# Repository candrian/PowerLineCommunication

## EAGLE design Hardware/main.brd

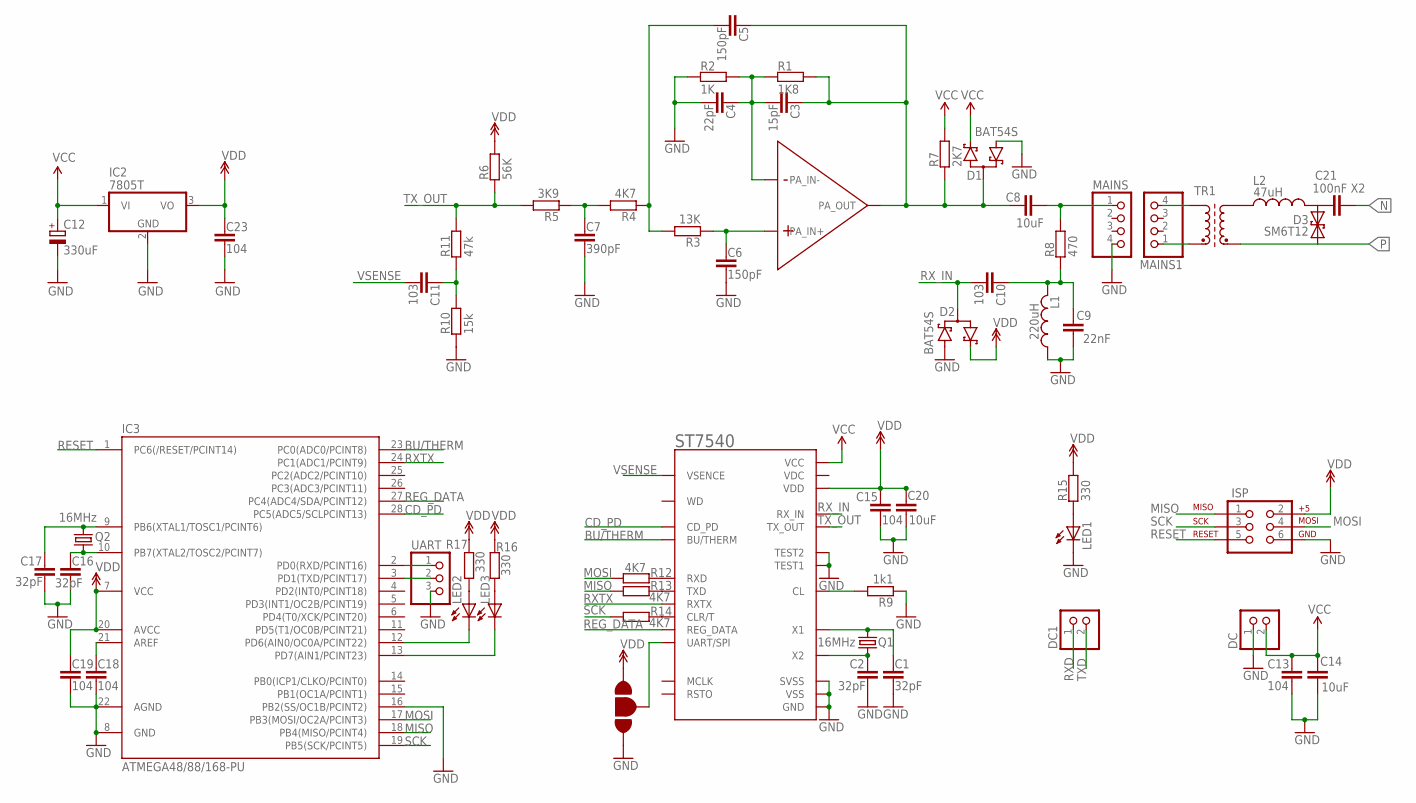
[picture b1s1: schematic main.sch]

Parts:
C1, C2, C16, C17: 32pF; C-22X55(FAKI)
C3: 15pF; C-22X55(FAKI)
C4: 22pF; C-22X55(FAKI)
C5: 150pF; C-22X55(FAKI)
C6: 150pF; C-25X8(FAKI)
C7: 390pF; C-25X8(FAKI)
C8: 10uF; C-25X8(FAKI)
C9: 22nF; C-22X6(FAKI)
C10, C11: 103; C-25X8(FAKI)
C12: 330uF; TT2D6
C13, C15, C18, C19: 104; C-22X6(FAKI)
C14, C20: 10uF; C-22X55(FAKI)
C21: 100nF X2; C-22X6(FAKI)
C23: 104; C-22X55(FAKI)
D1, D2: BAT54S; SOT23
D3: SM6T12; F126Z12
DC, DC1: PINHD-1X2; 1X02
IC1: ST7540BREAKOUT; ST7540-BREAKOUT
IC2: 7805T; TO220H
IC3: ATMEGA48/88/168-PU; DIL28-3
ISP: AVR-ISP-6
JP2: PCB-JUMPER-3
L1: 220uH; L-2.2MH-DIP
L2: 47uH; L-2.2MH-DIP
LED1, LED2, LED3: LED3MM
MAINS, MAINS1: PINHD-1X4; 1X04
Q1, Q2: 16MHz; HC49US
R1: 1K8; R0207/12
R2: 1K; R0207/12
R3: 13K; R0207/12
R4: 4K7; R0207/12
R5: 3K9; R0207/12
R6: 56K; R0207/12
R7: 2K7; R0207/12
R8: 470; R0207/12
R9: 1k1; R0207/12
R10: 15k; R0207/12
R11: 47k; R0207/12
R12, R13, R14: 4K7; R0270/10
R15, R16, R17: 330; R0270/10
TR1: SM-T4
UART: PINHD-1X3; 1X03

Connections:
12V: C15.1, C19.1, C20.1, C23.1, D2.2 (C2), IC1.VDD, IC2.3 (VO), IC3.7 (VCC), IC3.20 (AVCC), ISP.2, JP2.P$1 (1), R6.2, R15.2, R16.2, R17.2
BU/THERM: IC1.BU/THERM, IC3.23 (PC0(ADC0/PCINT8))
CD_PD: IC1.CD_PD, IC3.28 (PC5(ADC5/SCLPCINT13))
GND: C1.2, C2.2, C4.2, C6.2, C7.2, C9.1, C12.-, C13.2, C14.2, C15.2, C16.2, C17.2, C18.2, C19.2, C20.2, C23.2, D1.1 (A1), D2.1 (A1), DC.1, IC1.GND, IC1.SVSS, IC1.TEST1, IC1.TEST2, IC1.VSS, IC2.2 (GND), IC3.8 (GND), IC3.16 (PB2(SS/OC1B/PCINT2)), IC3.22 (AGND), ISP.6, JP2.P$3 (3), L1.P$1 (1), LED1.K (C), MAINS.4, R2.1, R9.1, R10.1, UART.3
MISO: IC3.18 (PB4(MISO/PCINT4)), ISP.1, R13.1
MOSI: IC3.17 (PB3(MOSI/OC2A/PCINT3)), ISP.4, R12.1
N: C21.1
unnamed: C1.1, IC1.X1, Q1.1
unnamed: C2.1, IC1.X2, Q1.2
unnamed: C3.1, C5.1, C8.1, D1.3 (C1A2), IC1.PA_OUT, R1.2, R7.1
unnamed: C3.2, C4.1, IC1.PA_IN-, R1.1, R2.2
unnamed: C5.2, R3.2, R4.1
unnamed: C6.1, IC1.PA_IN+, R3.1
unnamed: C8.2, MAINS.1, R8.2
unnamed: C7.1, R4.2, R5.1
unnamed: C9.2, C10.1, L1.P$2 (2), R8.1
unnamed: C11.1, R10.2, R11.1
unnamed: IC1.CL, R9.2
unnamed: IC1.UART/SPI, JP2.P$2 (2)
unnamed: C16.1, IC3.10 (PB7(XTAL2/TOSC2/PCINT7)), Q2.2
unnamed: C17.1, IC3.9 (PB6(XTAL1/TOSC1/PCINT6)), Q2.1
unnamed: MAINS1.4, TR1.1 (A1)
unnamed: MAINS1.1, TR1.2 (E1)
unnamed: IC1.CLR/T, R14.2
unnamed: C18.1, IC3.21 (AREF)
unnamed: LED1.A, R15.1
unnamed: IC3.12 (PD6(AIN0/OC0A/PCINT22)), LED2.K (C)
unnamed: IC3.13 (PD7(AIN1/PCINT23)), LED3.K (C)
unnamed: LED2.A, R17.1
unnamed: LED3.A, R16.1
unnamed: L2.P$1 (1), TR1.5 (A2)
unnamed: C21.2, D3.C (2), L2.P$2 (2)
P: D3.A (1), TR1.4 (E2)
REG_DATA: IC1.REG_DATA, IC3.27 (PC4(ADC4/SDA/PCINT12))
RESET: IC3.1 (PC6(/RESET/PCINT14)), ISP.5
RXD: DC1.1, IC1.RXD, IC3.2 (PD0(RXD/PCINT16)), R12.2, UART.1
RXTX: IC1.RXTX, IC3.24 (PC1(ADC1/PCINT9))
RX_IN: C10.2, D2.3 (C1A2), IC1.RX_IN
SCK: IC3.19 (PB5(SCK/PCINT5)), ISP.3, R14.1
TXD: DC1.2, IC1.TXD, IC3.3 (PD1(TXD/PCINT17)), R13.2, UART.2
TX_OUT: IC1.TX_OUT, R5.2, R6.1, R11.2
VCC: C12.+, C13.1, C14.1, D1.2 (C2), DC.2, IC1.VCC, IC2.1 (VI), R7.2
VSENSE: C11.2, IC1.VSENSE (VSENCE)

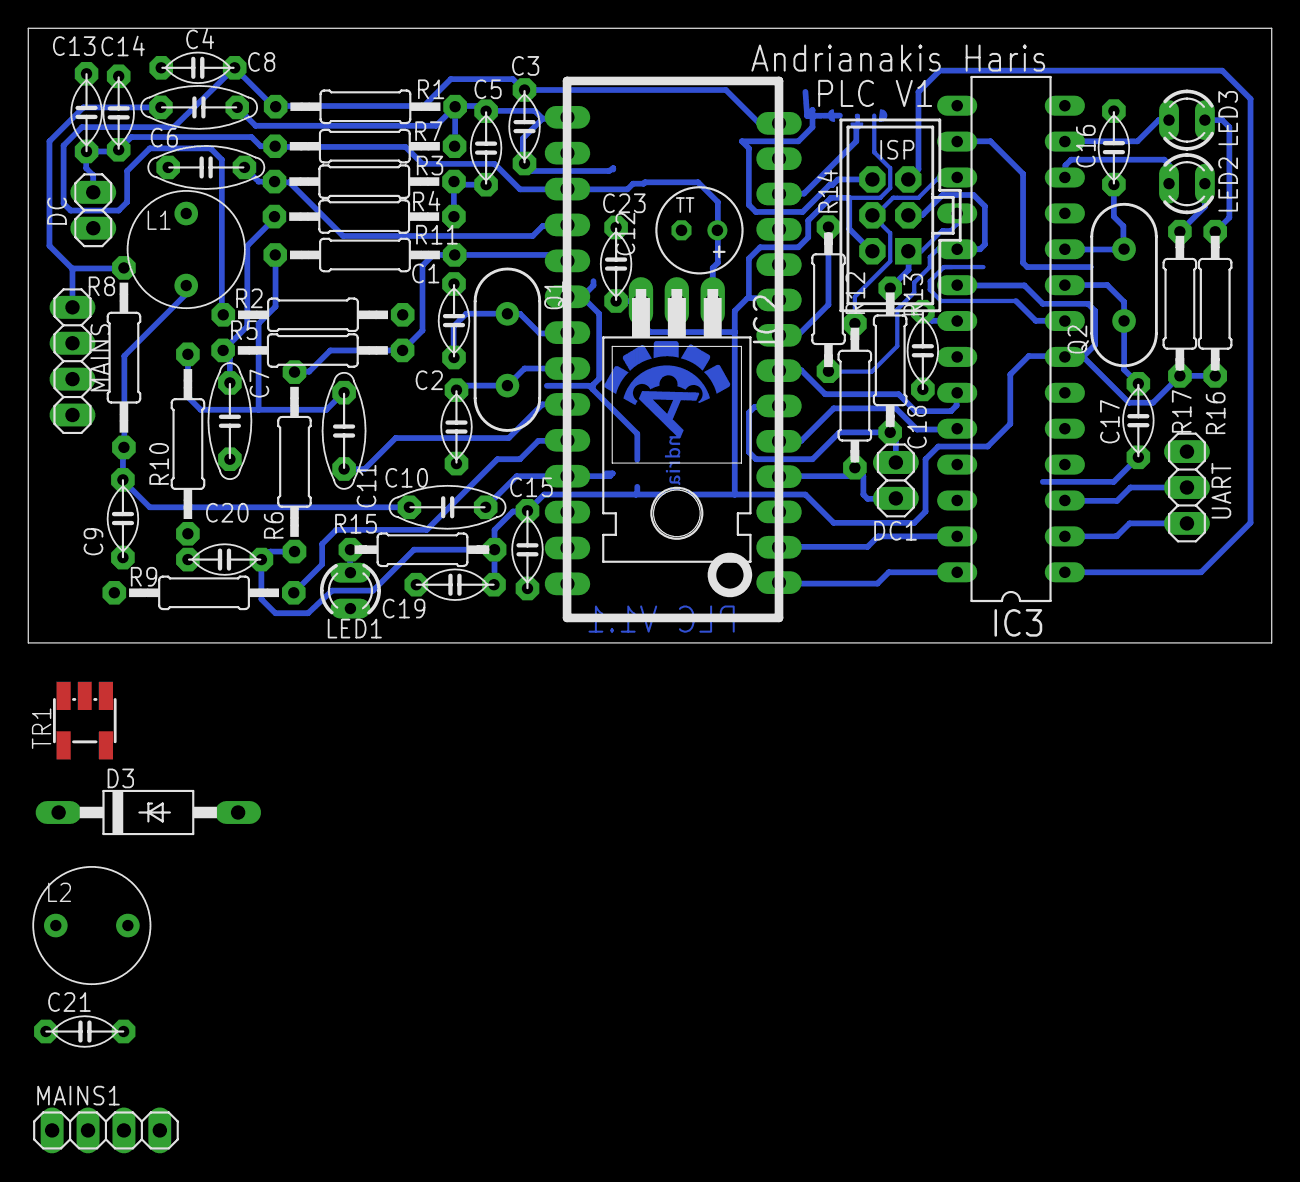
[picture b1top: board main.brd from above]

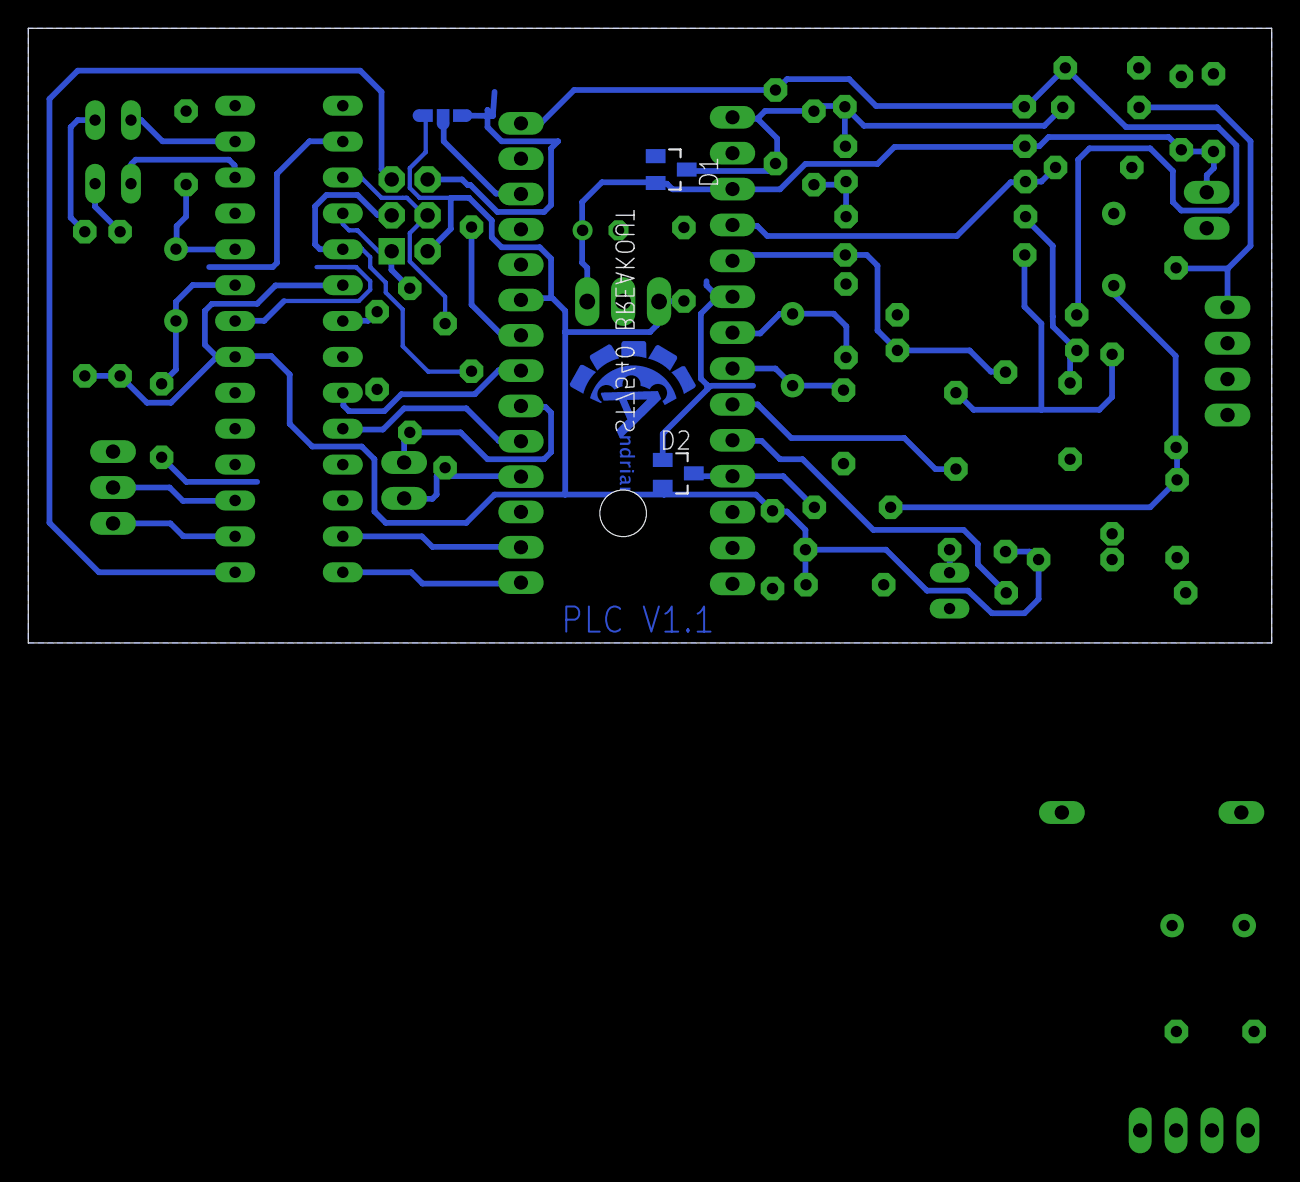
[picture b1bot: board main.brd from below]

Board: 2 copper layers, 88.0 x 43.5 mm, 61 parts (2 on the bottom side), 42 nets.

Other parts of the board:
U$1: CANDRIAN-LOGO/SMALL/BOTTOM

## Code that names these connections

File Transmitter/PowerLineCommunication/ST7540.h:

#define DDR_BU_THERM    DDRC
#define DDR_RXTX        DDRC
#define DDR_REG_DATA    DDRC
#define DDR_CD_PD       DDRC

#define PORT_BU_THERM   PORTC
#define PORT_RXTX       PORTC
#define PORT_REG_DATA   PORTC
#define PORT_CD_PD      PORTC

#define PIN_CD_PD       PINC

#define BU_THERM        PC0
#define RXTX            PC1
#define REG_DATA        PC4
#define CD_PD           PC5

#define reg_acc()       PORT_REG_DATA   |=  (1<<REG_DATA);
#define data_acc()      PORT_REG_DATA   &=  ~(1<<REG_DATA);

#define tx_mode()       PORT_RXTX   &=  ~(1<<RXTX);
#define rx_mode()       PORT_RXTX   |=  (1<<RXTX);

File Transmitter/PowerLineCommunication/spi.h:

#define DDR_SPI     DDRB
#define PORT_SPI    PORTB
#define PIN_SPI     PINB

#define DDR_SS      DDRB
#define PORT_SS     PORTB

#define SS_PIN      PB1
#define SS          PB2
#define MOSI        PB3
#define MISO        PB4
#define SCK         PB5

#define ss_clear()  PORT_SS &=  ~(1<<SS_PIN);
#define ss_set()    PORT_SS |=  (1<<SS_PIN);
